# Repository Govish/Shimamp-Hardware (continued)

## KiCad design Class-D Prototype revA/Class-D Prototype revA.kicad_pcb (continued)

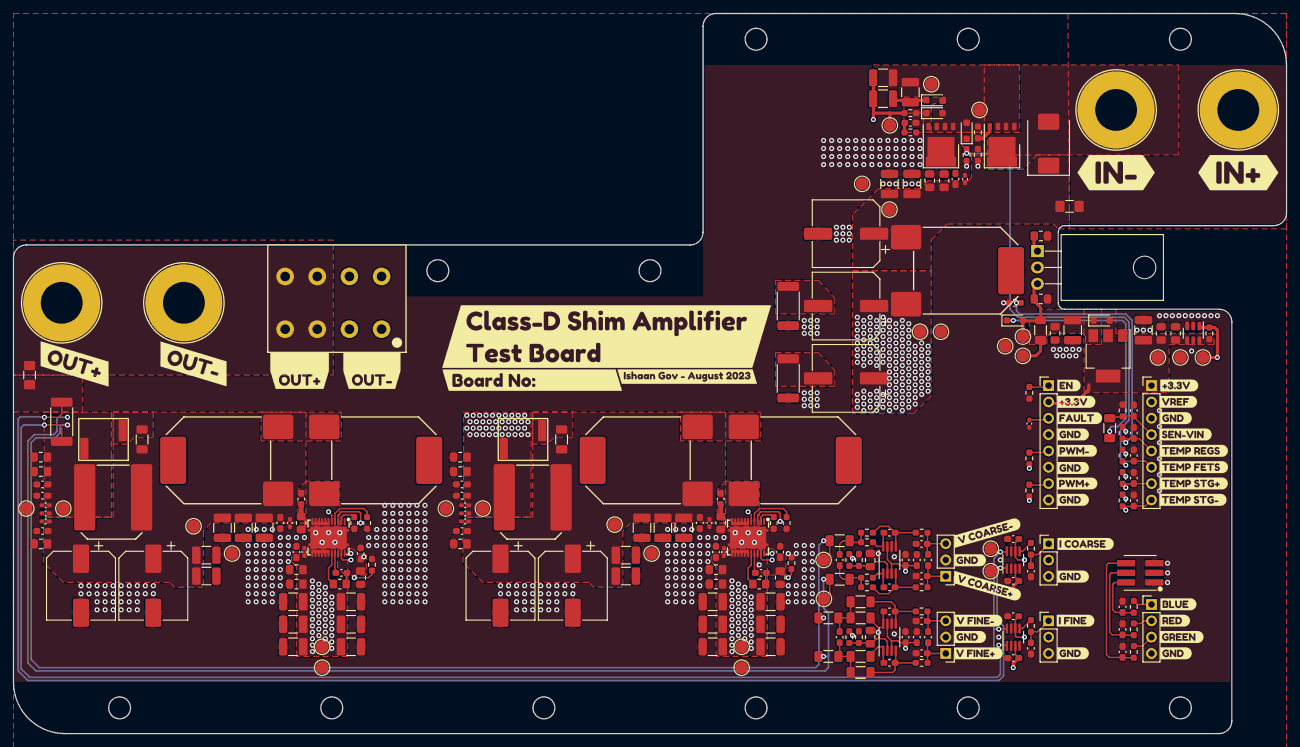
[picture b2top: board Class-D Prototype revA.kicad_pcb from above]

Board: 4 copper layers, 198.0 x 112.0 mm, 283 parts (0 on the bottom side), 81 nets.

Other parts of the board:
kibuzzard-64CF1C96: G***; kibuzzard-64CF1C96
kibuzzard-64CF1CEA: G***; kibuzzard-64CF1CEA
kibuzzard-64CF1E0D: G***; kibuzzard-64CF1E0D
kibuzzard-64CF1E1A: G***; kibuzzard-64CF1E1A
kibuzzard-64CF1E3D: G***; kibuzzard-64CF1E3D
kibuzzard-64CF1E8F: G***; kibuzzard-64CF1E8F
kibuzzard-64CF1E29: G***; kibuzzard-64CF1E29
kibuzzard-64CF1E34: G***; kibuzzard-64CF1E34
kibuzzard-64CF1E44: G***; kibuzzard-64CF1E44
kibuzzard-64CF1E82: G***; kibuzzard-64CF1E82
kibuzzard-64CF1EB5: G***; kibuzzard-64CF1EB5
kibuzzard-64CF1EC8: G***; kibuzzard-64CF1EC8
kibuzzard-64CF1ED1: G***; kibuzzard-64CF1ED1
kibuzzard-64CF1EE4: G***; kibuzzard-64CF1EE4
kibuzzard-64CF1F01: G***; kibuzzard-64CF1F01
kibuzzard-64CF1F4F: G***; kibuzzard-64CF1F4F
kibuzzard-64CF1F6F: G***; kibuzzard-64CF1F6F
kibuzzard-64CF1F11: G***; kibuzzard-64CF1F11
kibuzzard-64CF1F61: G***; kibuzzard-64CF1F61
kibuzzard-64CF1F69: G***; kibuzzard-64CF1F69
kibuzzard-64CF1F79: G***; kibuzzard-64CF1F79
kibuzzard-64CF1FA1: G***; kibuzzard-64CF1FA1
kibuzzard-64CF1FAA: G***; kibuzzard-64CF1FAA
kibuzzard-64CF1FB5: G***; kibuzzard-64CF1FB5
kibuzzard-64CF22CA: G***; kibuzzard-64CF22CA
kibuzzard-64CF22E7: G***; kibuzzard-64CF22E7
kibuzzard-64CF24C8: G***; kibuzzard-64CF24C8
kibuzzard-64CF24F4: G***; kibuzzard-64CF24F4
kibuzzard-64CF222A: G***; kibuzzard-64CF222A
kibuzzard-64CF223D: G***; kibuzzard-64CF223D
kibuzzard-64CF2245: G***; kibuzzard-64CF2245
kibuzzard-64CF2417: G***; kibuzzard-64CF2417
kibuzzard-64CF2468: G***; kibuzzard-64CF2468
kibuzzard-64CFD6AE: G***; kibuzzard-64CFD6AE
kibuzzard-64CFD733: G***; kibuzzard-64CFD733
kibuzzard-64CFD751: G***; kibuzzard-64CFD751
kibuzzard-64CFDF40: G***; kibuzzard-64CFDF40
kibuzzard-64CFDF65: G***; kibuzzard-64CFDF65
kibuzzard-64CFDFD1: G***; kibuzzard-64CFDFD1

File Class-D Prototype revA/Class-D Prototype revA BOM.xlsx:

Class-D Shim Amplifier Prototype BOM - August 6, 2023
Reference | Qty | Qty 5 | Value | Footprint | Manufacturer | Part Number
C1, C2, C3, C5, C11, C32, C34, C35, C46, C48, C49, C59, C60, C65, C66, C77, C78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 | 28 | 140 | 100n | Capacitor_SMD:C_0603_1608Metric_Pad1.08x0.95mm_HandSolder | Samsung Electro-Mechanics | CL10B104KB8NNWC
C4, C7, C8, C18, C21, C23, C24, C25, C26, C27, C28, C37, C38, C39, C40, C41, C4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 | 27 | 135 | 22u | Capacitor_SMD:C_1210_3225Metric_Pad1.33x2.70mm_HandSolder | Samsung Electro-Mechanics | CL32B226KAJNNNE
C6, C13, C14 | 3 | 15 | 330u | Capacitor_SMD:CP_Elec_10x12.6 | Wurth Elektronik | 875075661010
C9, C10, C15, C17, C19, C20, C29, C43, C58, C76 | 10 | 50 | 4.7u | Capacitor_SMD:C_0805_2012Metric_Pad1.18x1.45mm_HandSolder | Samsung Electro-Mechanics | CL21A475KLCLQNC
C12, C22, C31, C45, C61, C62, C67, C68, C79, C80, C85, C86 | 12 | 60 | 4.7n | Capacitor_SMD:C_0402_1005Metric_Pad0.74x0.62mm_HandSolder | Samsung Electro-Mechanics | CL05B472KB5NNN
C16, C30, C33, C44, C47, C63, C64, C81, C82, C97, C106 | 11 | 55 | 1u | Capacitor_SMD:C_0805_2012Metric_Pad1.18x1.45mm_HandSolder | Samsung Electro-Mechanics | CL21B105KBFNNNG
C36, C50, C102 | 3 | 15 | 150p | Capacitor_SMD:C_0603_1608Metric_Pad1.08x0.95mm_HandSolder | Murata Electronics | GCM1885C2A151JA16D
C51, C52, C69, C70 | 4 | 20 | 220u | Capacitor_SMD:CP_Elec_10x12.5 | Wurth Elektronik | 875075561008
C93, C94, C98, C99, C100, C103, C107, C108, C109, C110, C112, C113, C115 | 13 | 65 | 1n | Capacitor_SMD:C_0603_1608Metric_Pad1.08x0.95mm_HandSolder | Murata Electronics | GCM1885C2A102FA16D
C95, C96 | 2 | 10 | 470p | Capacitor_SMD:C_0603_1608Metric_Pad1.08x0.95mm_HandSolder | Murata Electronics | GCM1885C2A471FA16D
C104, C105 | 2 | 10 | 33p | Capacitor_SMD:C_0603_1608Metric_Pad1.08x0.95mm_HandSolder | Murata Electronics | GCM1885C2A330JA16D
D1 | 1 | 5 | RGB | Custom-DiscreteSemi:LED_RGB_5050-6-WURTH | Wurth Elektronik | 150505M173300
D2 | 1 | 5 | 20V | Diode_SMD:D_SMC | SMC Diode Solutions | SMCJ20CA
D3, D5 | 2 | 10 | 10V | Diode_SMD:D_SOD-323_HandSoldering | onsemi | MM3Z10VC
D4, D6, D7 | 3 | 15 | NSR0340HT1G | Diode_SMD:D_SOD-323_HandSoldering | SMC Diode Solutions | DSS16U
F1 | 1 | 5 | 25A | Fuse:Fuse_1206_3216Metric_Pad1.42x1.75mm_HandSolder | Bel Fuse Inc. | 0685H9250-01
F2 | 1 | 5 | 12A | Fuse:Fuse_1206_3216Metric_Pad1.42x1.75mm_HandSolder | Bel Fuse Inc. | 0685H9120-01
J7, J8, J11, J12 | 4 | 20 | 6095 | Custom-Electromechanical:Keystone 6095 | Keystone Electronics | 6095
J10 | 1 | 5 | 2604-3104 | Custom-Connector:Wago_2604-3104 | WAGO Corporation | 2604-3104
L1, L2, L3, L6, L7 | 5 | 25 | 257n | Custom-RLC:COILCRAFT_2014 | Coilcraft | 2014VS-251MED
L4, L8 | 2 | 10 | 90n | Custom-RLC:COILCRAFT_1212 | Coilcraft | 2014VS-251MED
L5, L9 | 2 | 10 | 22n | Custom-RLC:WURTH_3168 | Wurth Elektronik | 744914122
PAD1 | 1 | 5 | 173-7-220P | - | Wakefield-Vette | 173-7-220P
Q1, Q2 | 2 | 10 | SIRA60DP | Package_DFN_QFN:PQFN-8-EP_6x5mm_P1.27mm_Generic | Vishay Siliconix | SIRA60DP-T1-GE3
R1, R2, R3, R13, R58, R59 | 6 | 30 | 750R | Resistor_SMD:R_0603_1608Metric_Pad0.98x0.95mm_HandSolder | Stackpole Electronics Inc | RMCF0603FT750R
R4, R14, R27, R31, R33, R35, R46, R47, R56, R57 | 10 | 50 | 4.7k | Resistor_SMD:R_0603_1608Metric_Pad0.98x0.95mm_HandSolder | Stackpole Electronics Inc | RMCF0603FT4K70
R5, R8 | 2 | 10 | 100k | Resistor_SMD:R_0603_1608Metric_Pad0.98x0.95mm_HandSolder | Stackpole Electronics Inc | RMCF0603FT100K
R6, R7 | 2 | 10 | 1k 1/2W | Resistor_SMD:R_1210_3225Metric_Pad1.30x2.65mm_HandSolder | Stackpole Electronics Inc | RMCF1210JT1K00
R9, R15, R16 | 3 | 15 | 22R | Resistor_SMD:R_0603_1608Metric_Pad0.98x0.95mm_HandSolder | Stackpole Electronics Inc | RMCF0603FT22R0
R10, R11 | 2 | 10 | 50mR | Resistor_SMD:R_2512_6332Metric_Pad1.40x3.35mm_HandSolder | Stackpole Electronics Inc | CSRN2512FK50L0
R12 | 1 | 5 | 500m | Resistor_SMD:R_1206_3216Metric_Pad1.30x1.75mm_HandSolder | Stackpole Electronics Inc | CSR1206FKR500
R17, R20, R21, R24 | 4 | 20 | 2.2R | Resistor_SMD:R_0805_2012Metric_Pad1.20x1.40mm_HandSolder | Stackpole Electronics Inc | RMCF0603FT100K
R25, R26 | 2 | 10 | 120m | Resistor_SMD:R_1206_3216Metric_Pad1.30x1.75mm_HandSolder | Eaton - Electronics Division | MFHA1206R1200FC
R28, R32, R34, R36 | 4 | 20 | 10k NTC | Resistor_SMD:R_0603_1608Metric_Pad0.98x0.95mm_HandSolder | EPCOS - TDK Electronics | B57330V2103F260
R29, R38, R39, R48, R49, R50, R51, R52, R53 | 9 | 45 | 2.2k 0.1% | Resistor_SMD:R_1206_3216Metric_Pad1.30x1.75mm_HandSolder | KOA Speer Electronics, Inc. | RN73R2BTTD2201B25
R30, R40, R41, R42, R43 | 5 | 25 | 220R 0.1% | Resistor_SMD:R_0603_1608Metric_Pad0.98x0.95mm_HandSolder | KOA Speer Electronics, Inc. | RN73R1JTTD2200B25
R37 | 1 | 5 | 10mR 4W | Custom-RLC:R_2512_6332_CURRENT_SHUNT | Isabellenhuette USA | VMS-R010-1.0-U
R44, R45, R54, R55 | 4 | 20 | 75R 0.1% | Resistor_SMD:R_0603_1608Metric_Pad0.98x0.95mm_HandSolder | KOA Speer Electronics, Inc. | RN73R1JTTD75R0B25
U1 | 1 | 5 | MC7805ACTG | Package_TO_SOT_THT:TO-220-3_Horizontal_TabDown | onsemi | MC7805ACTG
U2 | 1 | 5 | MCP1501T-20E/CHY | Package_TO_SOT_SMD:SOT-23-6 | Microchip Technology | MCP1501T-20E/CHY
U3 | 1 | 5 | SPX1117M3-L-3-3/TR | Package_TO_SOT_SMD:SOT-223-3_TabPin2 | MaxLinear, Inc. | SPX1117M3-L-3-3/TR
U4, U5 | 2 | 10 | CSD95372AQ5M | Custom-IC:LSON-12-1EP_5x6mm | Texas Instruments | CSD95372AQ5M
U6, U7 | 2 | 10 | LTC6362 | Package_SO:MSOP-8_3x3mm_P0.65mm | Analog Devices Inc. | LTC6362CMS8#TRPBF
U8 | 1 | 5 | INA241A4 | Package_TO_SOT_SMD:SOT-23-8_Handsoldering | Texas Instruments | INA241A4IDDFR
U9 | 1 | 5 | INA241A1 | Package_TO_SOT_SMD:SOT-23-8_Handsoldering | Texas Instruments | INA241A1IDDFR
W1 | 1 | 5 | INSULATING WASHER | - | Assmann WSW Components | V5359
J1, J2 | 2 |  | DNP | Connector_PinHeader_2.54mm:PinHeader_1x08_P2.54mm_Vertical | - | -
J3, J4, J5, J6 | 4 |  | DNP | Connector_PinHeader_2.54mm:PinHeader_1x03_P2.54mm_Vertical | - | -
J9 | 1 |  | DNP | Connector_PinHeader_2.54mm:PinHeader_1x04_P2.54mm_Vertical | - | -
R18, R19, R22, R23 | 4 |  | DNP | Custom-RLC:DNP_R_0603_1608Metric_Pad0.98x0.95mm_HandSolder | - | -

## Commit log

2023-11-08 Pushing hardware revisions to GitHub
